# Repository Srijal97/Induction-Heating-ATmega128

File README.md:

# Induction-Heating-ATmega128
Code and other files for the control of Induction Heating of metals for temperatures up to 1200C+ for Riddhi Heatron. Control board uses the ATmega128 microcontroller.

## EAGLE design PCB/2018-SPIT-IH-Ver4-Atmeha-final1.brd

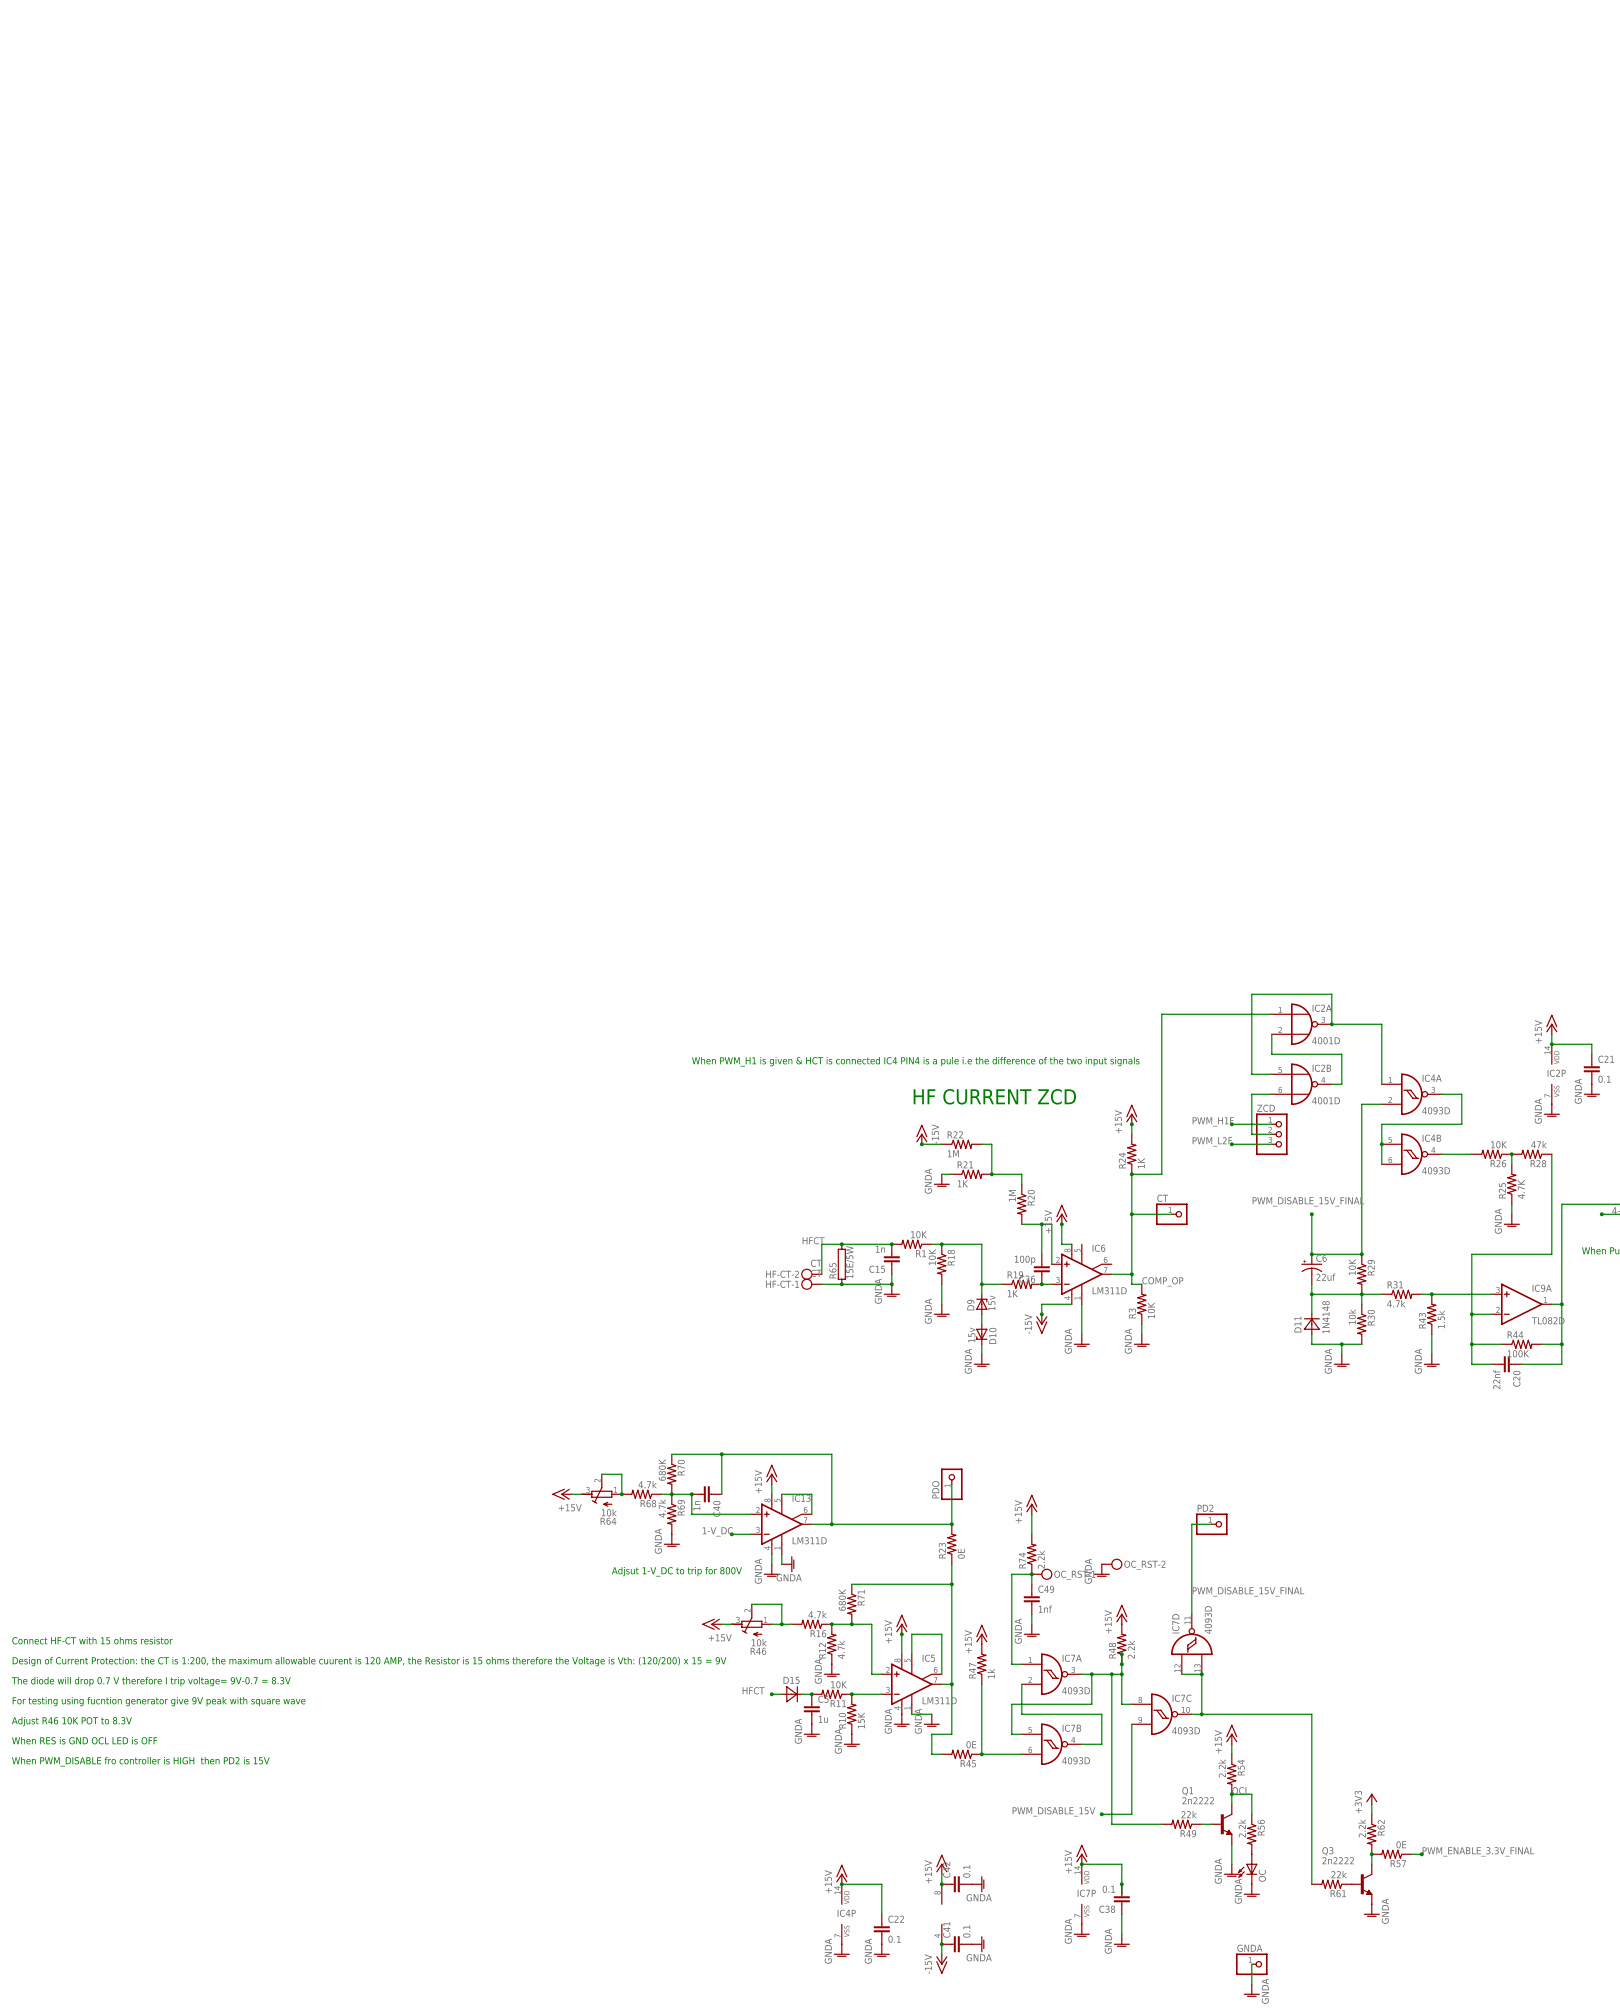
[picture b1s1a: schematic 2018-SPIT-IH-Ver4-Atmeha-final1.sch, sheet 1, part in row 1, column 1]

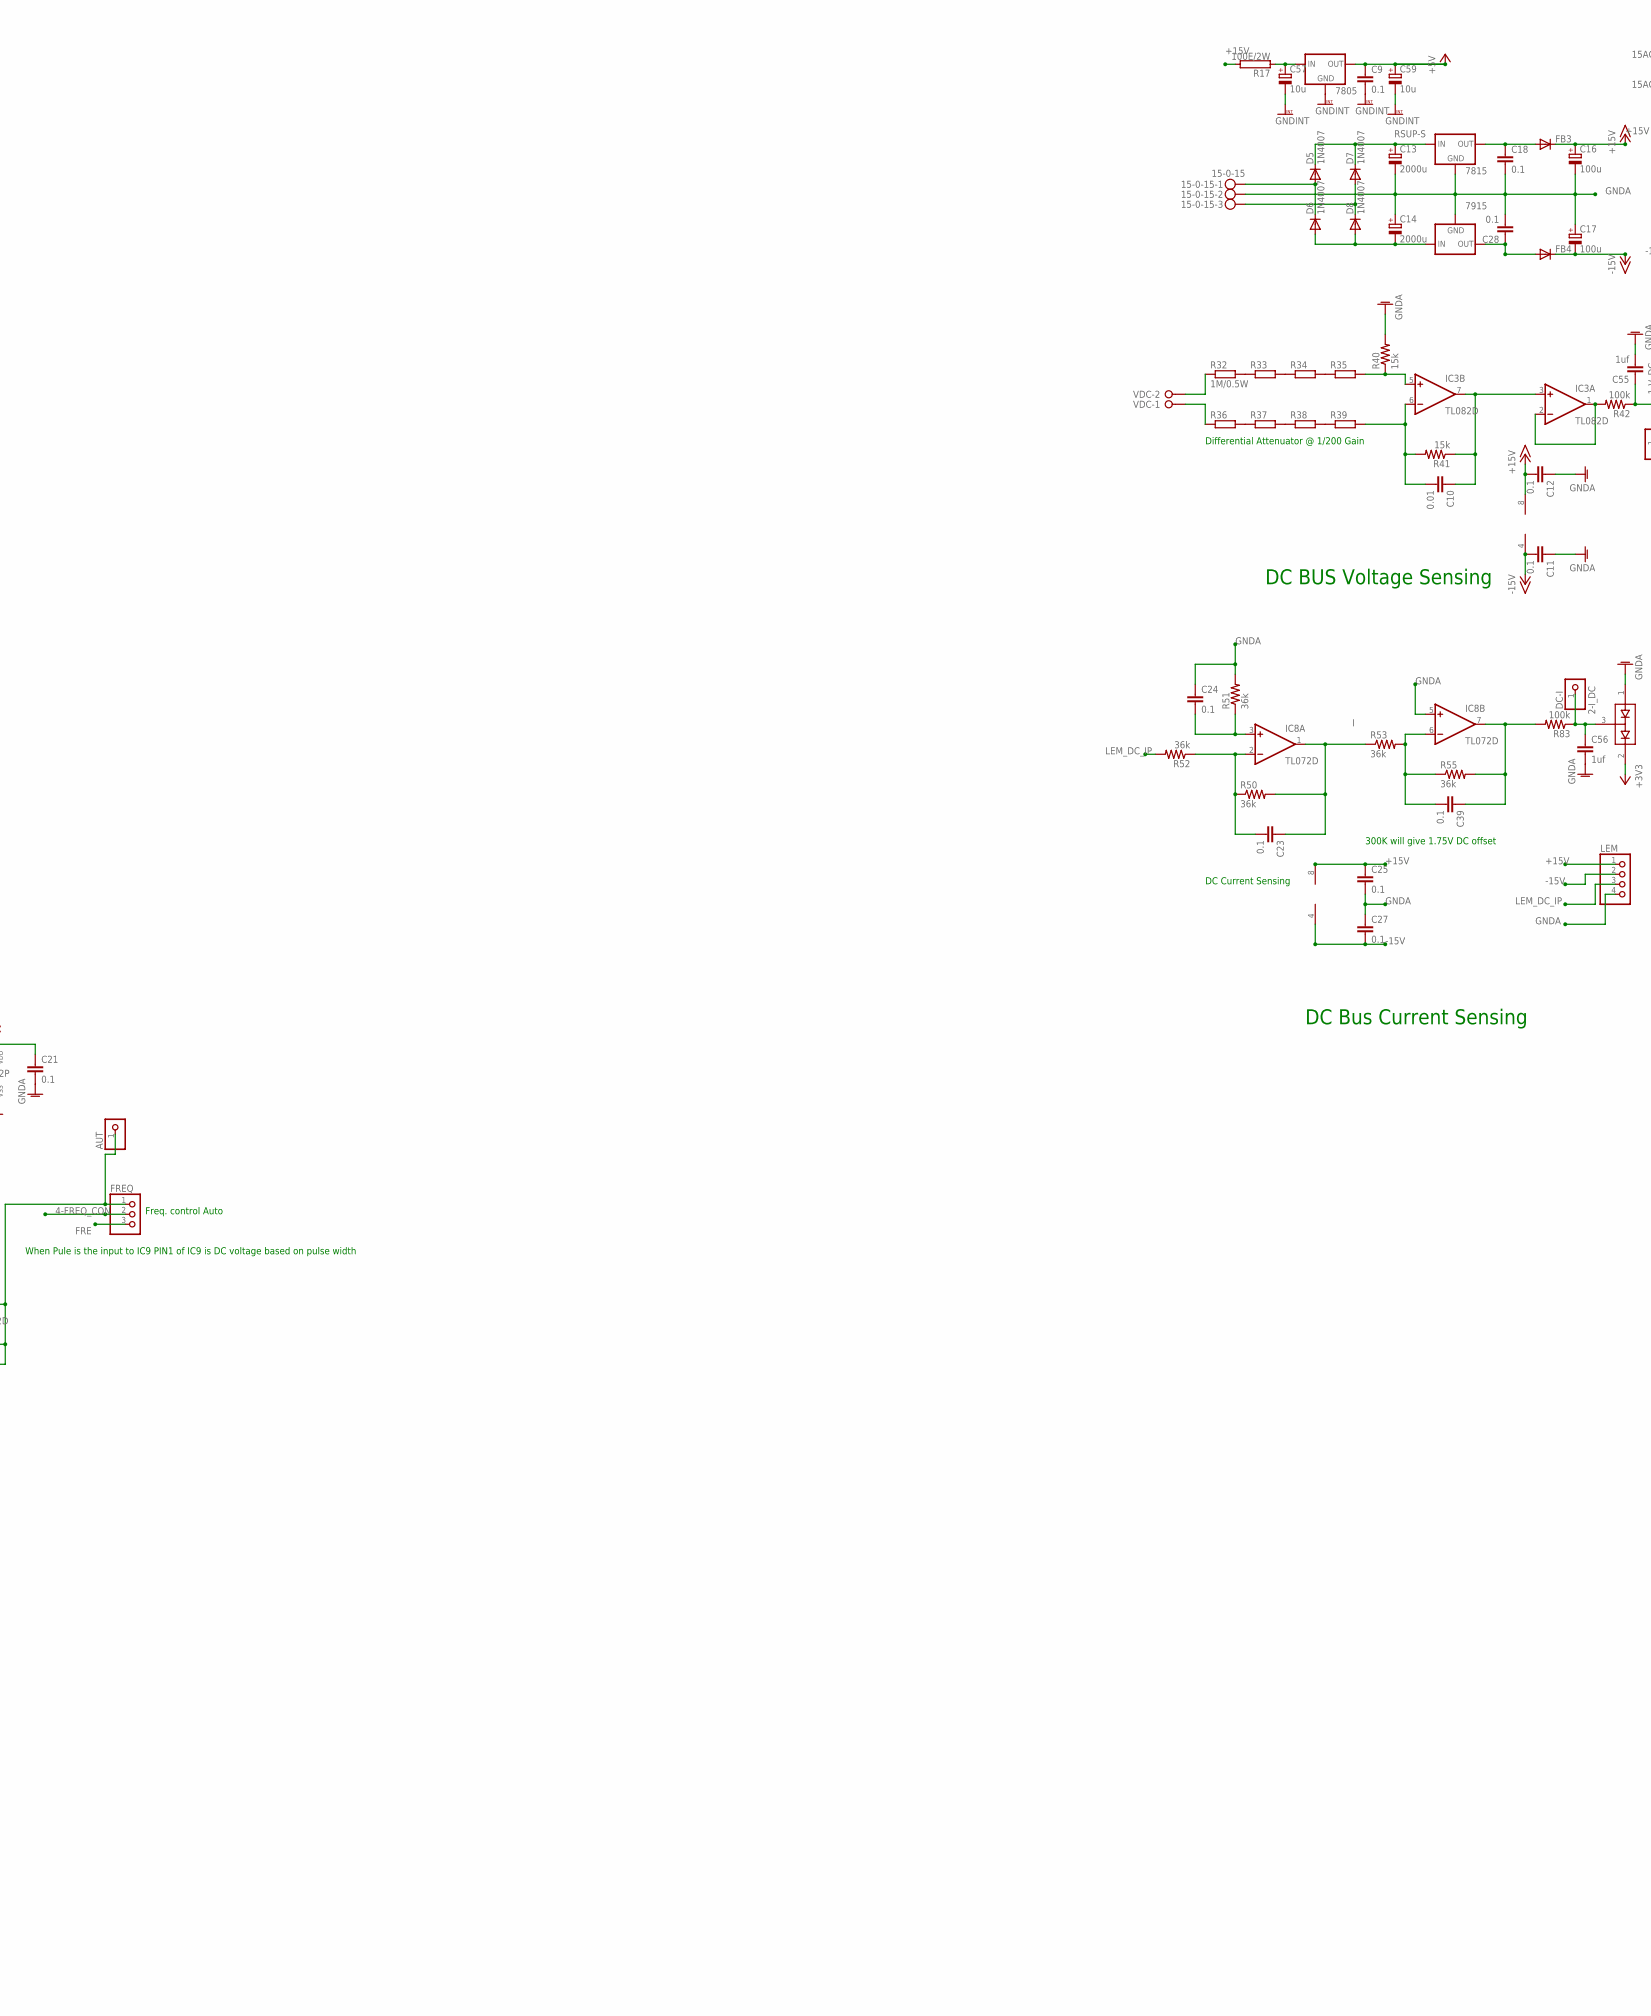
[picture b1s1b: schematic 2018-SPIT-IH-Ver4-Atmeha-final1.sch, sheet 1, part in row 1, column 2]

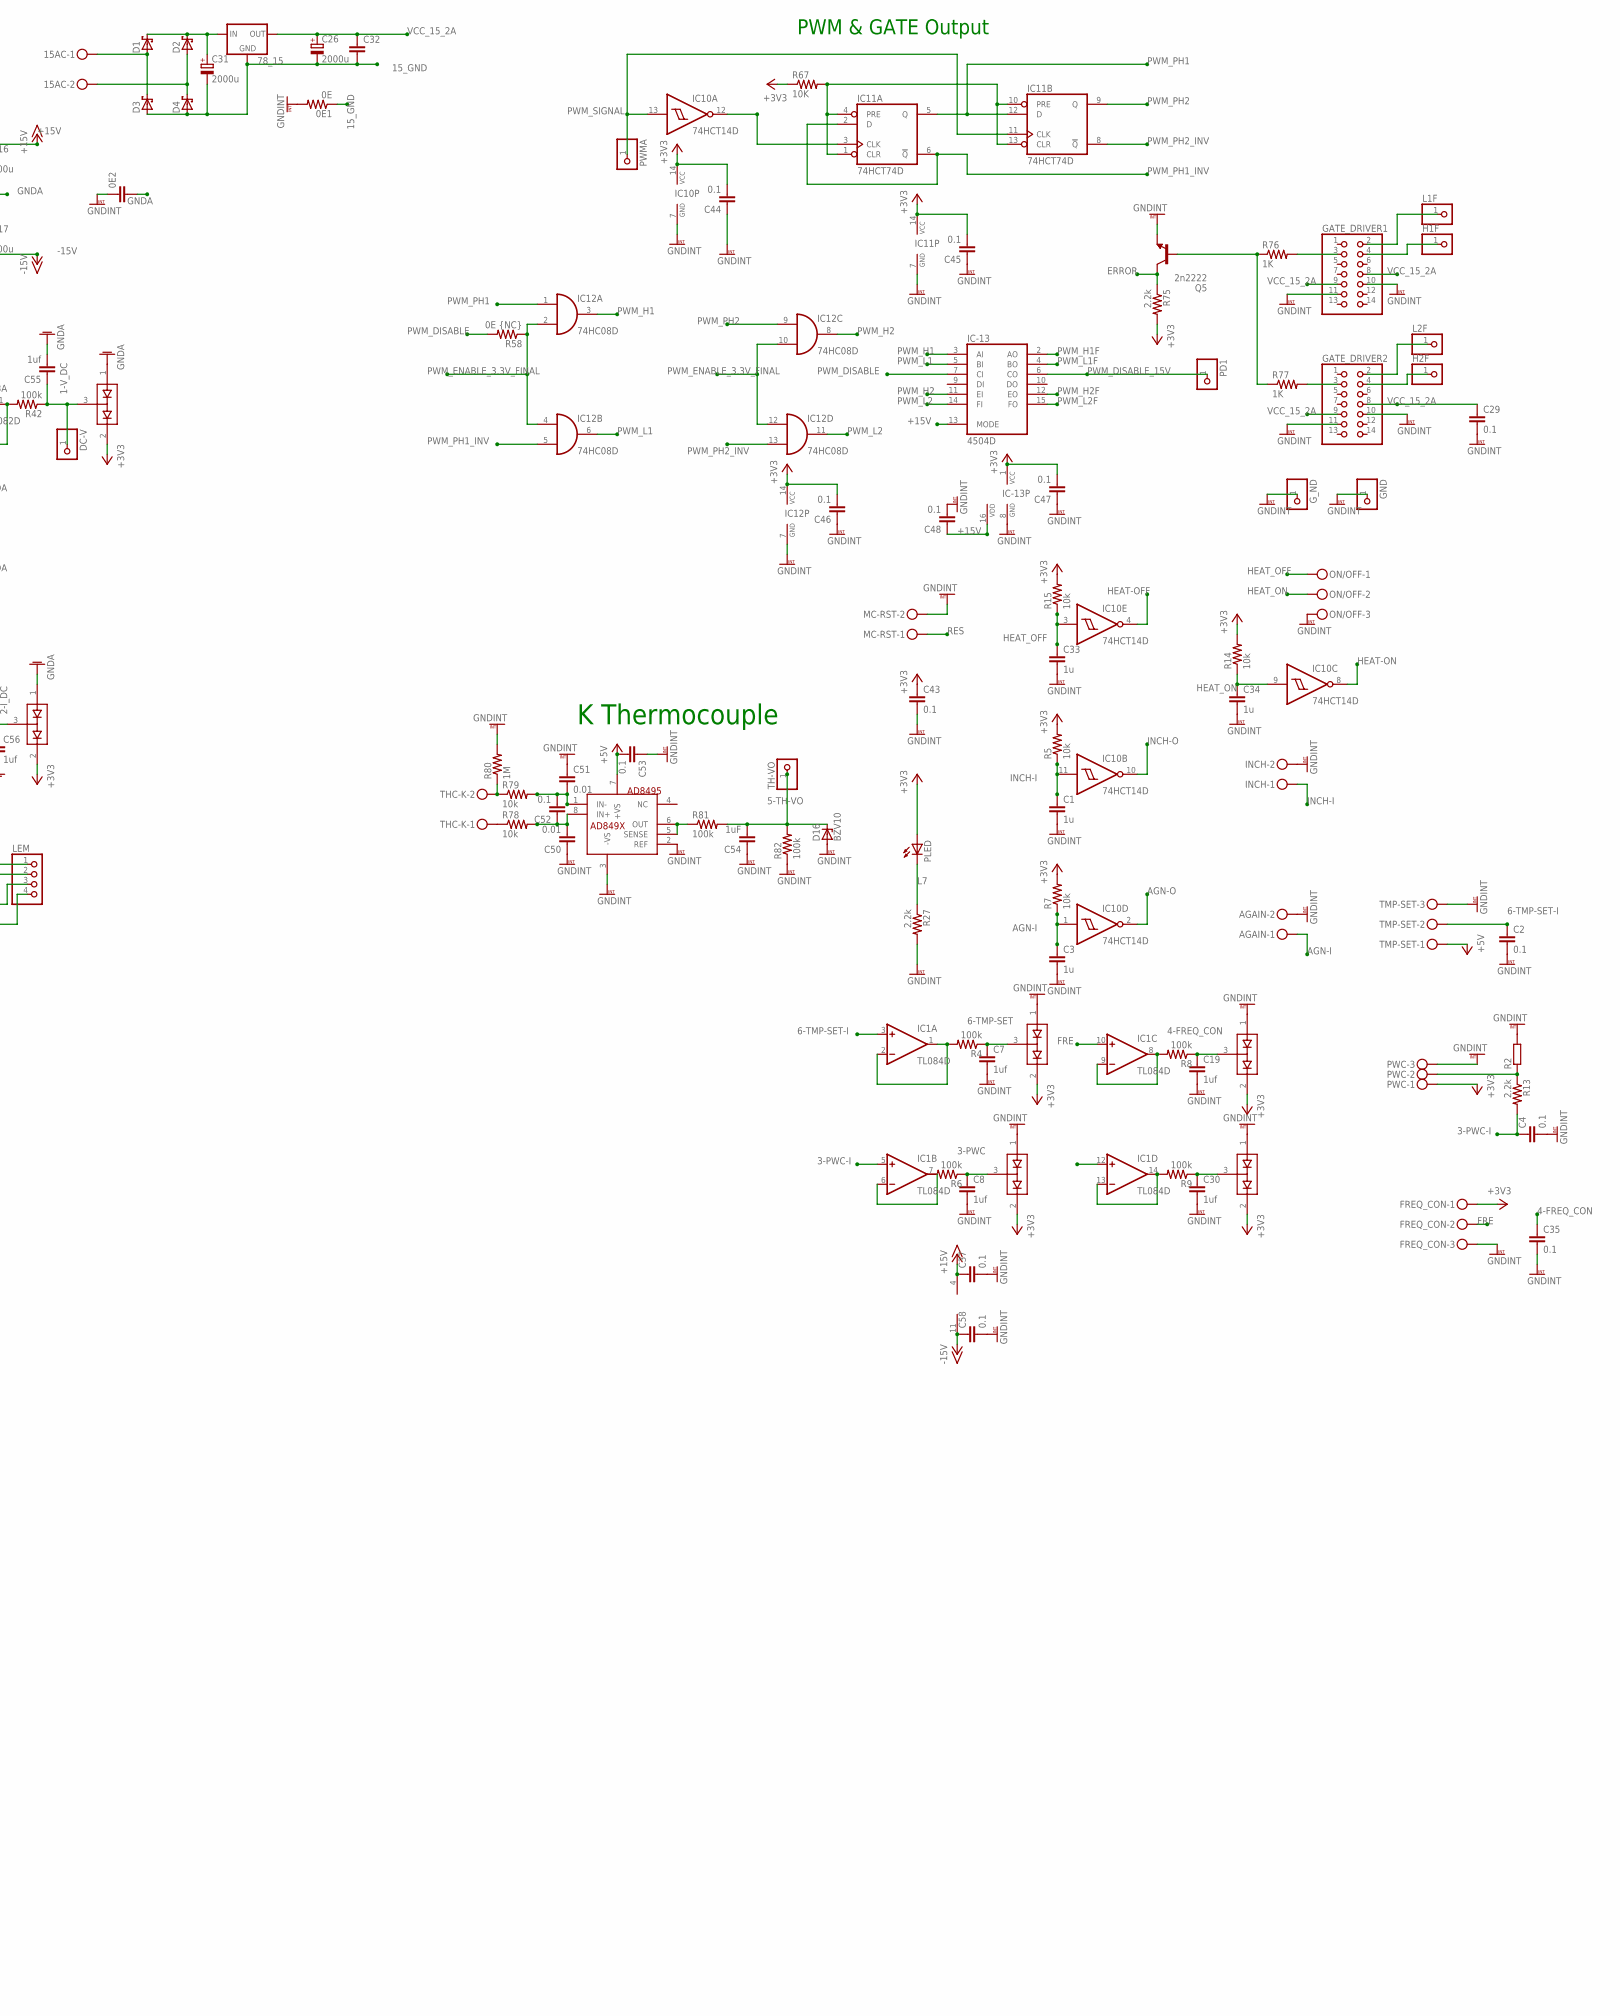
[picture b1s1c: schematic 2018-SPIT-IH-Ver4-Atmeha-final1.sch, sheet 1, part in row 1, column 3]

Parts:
0E1: 0E; M1206
0E2: C1206
15-0-15: 15-0-15; MKDSN1,5/3-5,08
15AC: MKDSN1,5/2-5,08
78_15: 78XX-TO3; TO3-78
7805, 7815: 78XXS
7915: 79XXS
AD8495: AD849X; MSOP8
AGAIN: MKDSN1,5/2-5,08; MPN MKDSN 1,5/2-5.08
AUT: PINHD-1X1; 1X01
C1, C3, C5, C33, C34: 1u; C1206
C2, C4, C9, C11, C12, C18, C21, C22, C23, C24, C25, C27, C28, C29, C35, C37, C38, C39, C41, C42, C43, C44, C45, C46, C47, C48, C52, C53, C58: 0.1; C1206
C6: 22uf; E2,5-6
C7, C8, C19, C30, C55, C56: 1uf; C1206
C10, C50, C51: 0.01; C1206
C13, C14: 2000u; E5-13
C15, C40: 1n; C1206
C16, C17: 100u; E5-8,5
C20: 22nf; C1206
C26, C31: 2000u; E7,5-18
C32: C-EU025-025X050; C025-025X050
C36: 100p; C1206
C49: 1nf; C1206
C54: 1uF; C1206
C57, C59: 10u; R/2012-12R
CT: PINHD-1X1; 1X01
D1, D2, D3, D4: C4111-15
D5, D6, D7, D8: 1N4007; DO41-10
D9, D10: 15v; DO34Z7
D11: 1N4148; SMA
D12, D14, D17, D18, D19, D20: BAV99; SOT23
D15: SMA
D16: BZV10; DO34Z7
DC-I: PINHD-1X1; 1X01
DC-V: PINHD-1X1; 1X01
FB3, FB4: SOD57-10
FREQ: PINHD-1X3; 1X03
FREQ_CON: MKDSN1,5/3-5,08
GATE_DRIVER1, GATE_DRIVER2: PINHD-2X7; 2X07
GND: PINHD-1X1; 1X01
GNDA: PINHD-1X1; 1X01
G_ND: PINHD-1X1; 1X01
H1F, H2F: PINHD-1X1; 1X01
HF-CT: CT; MKDSN1,5/2-5,08
IC1: TL084D; SO14
IC2: 4001D; SO14
IC3, IC9: TL082D; SO08
IC4, IC7: 4093D; SO14
IC5, IC6, IC13: LM311D; SO08
IC8: TL072D; SO08
IC10: 74HCT14D; SO14
IC11: 74HCT74D; SO14
IC12: 74HC08D; SO14
IC-13: 4504D; SO16
INCH: MKDSN1,5/2-5,08; MPN MKDSN 1,5/2-5.08
L1F, L2F: PINHD-1X1; 1X01
LEM: PINHD-1X4; 1X04
MC-RST: MKDSN1,5/2-5,08
OC: LEDCHIPLED_1206; CHIPLED_1206
OC_RST: MKDSN1,5/2-5,08
ON/OFF: MKDSN1,5/3-5,08
PD1, PD2: PINHD-1X1; 1X01
PDO: PINHD-1X1; 1X01
PLED: LEDCHIPLED_1206; CHIPLED_1206
PWC: MKDSN1,5/3-5,08
PWMA: PINHD-1X1; 1X01
Q1, Q3, Q5: 2n2222; SOT23-BEC
R1, R3, R11, R18, R26, R29, R67: 10K; M1206
R2, R33, R34, R35, R36, R37, R38, R39: R-EU_0309/12; 0309/12
R4, R6, R8, R9, R42, R81, R82, R83: 100k; M1206
R5, R7, R14, R15, R30, R78, R79: 10k; M1206
R10: 15K; M1206
R12, R16, R31, R68, R69: 4.7k; M1206
R13, R27, R48, R54, R56, R62, R74, R75: 2.2k; M1206
R17: 100E/2W; CA5050
R19, R21, R24, R76, R77: 1K; M1206
R20, R22, R80: 1M; M1206
R23, R45, R57: 0E; M1206
R25: 4.7K; M1206
R28: 47k; M1206
R32: 1M/0.5W; 0309/12
R40, R41: 15k; M1206
R43: 1.5k; M1206
R44: 100K; M1206
R46, R64: 10k; RTRIM64W
R47: 1k; M1206
R49, R61: 22k; M1206
R50, R51, R52, R53, R55: 36k; M1206
R58: 0E {NC}; M1206
R65: 15E/5W; MPC71-5
R70, R71: 680K; M1206
TH-VO: PINHD-1X1; 1X01
THC-K: MKDSN1,5/2-5,08
TMP-SET: MKDSN1,5/3-5,08; MPN SMKDSN1,5/3-5,08
VDC: W237-2N
ZCD: PINHD-1X3; 1X03

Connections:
1-V_DC: C55.1, D12.3 (COM), DC-V.1, IC13.3 (-IN), R42.1; also elsewhere on the board
2: C39.1, IC8.7 (OUT), R55.2, R83.2
2-I_DC: C56.1, D14.3 (COM), DC-I.1, R83.1; also elsewhere on the board
3-PWC: C8.1, D18.3 (COM), R6.1; also elsewhere on the board
3-PWC-I: C4.1, IC1.5 (+IN), R13.2
4-FREQ_CON: C19.1, C35.1, D20.3 (COM), FREQ.2, R8.1; also elsewhere on the board
5-TH-VO: C54.2, D16.C, R81.2, R82.2, TH-VO.1; also elsewhere on the board
6-TMP-SET: C7.1, D17.3 (COM), R4.1; also elsewhere on the board
6-TMP-SET-I: C2.1, IC1.3 (+IN), TMP-SET.2
15_GND: 0E1.1, 78_15.3 (GND), C26.-, C31.-, C32.2, D3.A, D4.A
+5V: 7805.OUT, AD8495.7 (+VS), C9.1, C43.1, C44.2, C45.2, C46.2, C47.2, C53.2, C59.+, D12.2 (C2), D14.2 (C2), D17.2 (C2), D18.2 (C2), D19.2 (C2), D20.2 (C2), FREQ_CON.1, IC10.14 (VCC), IC11.14 (VCC), IC12.14 (VCC), IC-13.1 (VCC), PLED.A, PWC.1, R5.2, R7.2, R14.2, R15.2, R62.1, R67.1, R75.2, TMP-SET.1; also elsewhere on the board
+15V: C12.2, C16.+, C21.1, C22.1, C25.1, C37.1, C38.2, C42.1, C48.1, FB3.C, IC1.4 (V+), IC2.14 (VDD), IC3.8 (V+), IC4.14 (VDD), IC5.8 (V+), IC6.8 (V+), IC7.14 (VDD), IC8.8 (V+), IC9.8 (V+), IC13.8 (V+), IC-13.13 (MODE), IC-13.16 (VDD), LEM.1, R17.2, R24.2, R46.3 (A), R47.2, R48.2, R54.1, R64.3 (A), R74.2
-15V: C11.2, C17.-, C27.2, C41.1, C58.1, FB4.C, IC1.11 (V-), IC3.4 (V-), IC6.4 (V-), IC8.4 (V-), IC9.4 (V-), LEM.2, R22.1
AGN-I: AGAIN.1, C3.1, IC10.1 (I), R7.1
AGN-O: IC10.2 (O); also elsewhere on the board
COMP_OP: CT.1, IC2.1 (I0), IC6.7 (OUT), R3.2, R24.1
ERROR: Q5.C, R75.1; also elsewhere on the board
FRE: FREQ.3, FREQ_CON.2, IC1.10 (+IN)
GNDA: 0E2.2, 15-0-15.2, 7815.GND, 7915.GND, C5.2, C11.1, C12.1, C13.-, C14.+, C15.1, C16.-, C17.+, C18.2, C21.2, C22.2, C24.1, C25.2, C27.1, C28.2, C38.1, C41.2, C42.2, C49.2, C55.2, C56.2, D10.C, D11.A, D12.1 (A1), D14.1 (A1), GNDA.1, HF-CT.1, IC2.7 (VSS), IC4.7 (VSS), IC5.1 (GND), IC5.4 (V-), IC6.1 (GND), IC7.7 (VSS), IC8.5 (+IN), IC13.1 (GND), IC13.4 (V-), LEM.4, OC.C, OC_RST.2, Q1.E, Q3.E, R3.1, R10.1, R12.1, R18.2, R21.1, R25.1, R30.2, R40.2, R43.1, R51.2, R65.1, R69.2
GNDINT: 0E1.2, 0E2.1, 7805.GND, AD8495.2 (REF), AD8495.3 (-VS), AGAIN.2, C1.2, C2.2, C3.2, C4.2, C7.2, C8.2, C9.2, C19.2, C29.2, C30.2, C33.2, C34.2, C35.2, C37.2, C43.2, C44.1, C45.1, C46.1, C47.1, C48.2, C50.1, C51.1, C53.1, C54.1, C57.-, C58.2, C59.-, D16.A, D17.1 (A1), D18.1 (A1), D19.1 (A1), D20.1 (A1), FREQ_CON.3, GATE_DRIVER1.10, GATE_DRIVER1.11, GATE_DRIVER2.10, GATE_DRIVER2.11, GND.1, G_ND.1, IC10.7 (GND), IC11.7 (GND), IC12.7 (GND), IC-13.8 (GND), INCH.2, MC-RST.2, ON/OFF.3, PWC.3, Q5.E, R2.2, R27.2, R80.2, R82.1, TMP-SET.3; also elsewhere on the board
HEAT-OFF: IC10.4 (O); also elsewhere on the board
HEAT-ON: IC10.8 (O); also elsewhere on the board
HEAT_OFF: C33.1, IC10.3 (I), ON/OFF.1, R15.1
HEAT_ON: C34.1, IC10.9 (I), ON/OFF.2, R14.1
HFCT: C15.2, D15.A, HF-CT.2, R1.2, R65.2
I: C23.1, IC8.1 (OUT), R50.2, R53.1
INCH-I: C1.1, IC10.11 (I), INCH.1, R5.1
INCH-O: IC10.10 (O); also elsewhere on the board
L7: PLED.C, R27.1
LEM_DC_IP: LEM.3, R52.2
unnamed: IC1.1 (OUT), IC1.2 (-IN), R4.2
unnamed: IC4.3 (O), IC4.5 (I0), IC4.6 (I1)
unnamed: IC1.6 (-IN), IC1.7 (OUT)
unnamed: IC1.8 (OUT), IC1.9 (-IN), R8.2
unnamed: C49.1, IC7.1 (I0), OC_RST.1, R74.1
unnamed: IC1.13 (-IN), IC1.14 (OUT), R9.2
unnamed: IC2.2 (I1), IC2.4 (O)
unnamed: IC4.4 (O), R26.2
unnamed: AUT.1, C20.1, FREQ.1, IC9.1 (OUT), R44.2
unnamed: 15-0-15.1, D5.A, D6.C
unnamed: AD8495.8 (IN+), C50.2, C52.1, R78.2
unnamed: IC5.2 (+IN), R12.2, R16.1, R71.2
unnamed: IC2.3 (O), IC2.5 (I0), IC4.1 (I0)
unnamed: IC10.12 (O), IC11.3 (CLK)
unnamed: IC5.5 (ON), IC5.6 (ON/STR)
unnamed: IC5.3 (-IN), R10.2, R11.1
unnamed: PWC.2, R2.1, R13.1
unnamed: IC11.1 (CLR), IC11.4 (PRE), IC11.10 (PRE), IC11.13 (CLR), R67.2
unnamed: GATE_DRIVER1.3, R76.2
unnamed: IC5.7 (OUT), R23.1, R45.2, R71.1
unnamed: IC7.6 (I1), R45.1, R47.1
unnamed: C5.1, D15.C, R11.2
unnamed: R32.2, R33.1
unnamed: R33.2, R34.1
unnamed: R34.2, R35.1
unnamed: R36.2, R37.1
unnamed: 15-0-15.3, D7.A, D8.C
unnamed: 7915.IN, C14.-, D6.A, D8.A
unnamed: D9.C, R1.1, R18.1, R19.1
unnamed: 7805.IN, C57.+, R17.1
unnamed: 7815.OUT, C18.1, FB3.A
unnamed: R37.2, R38.1
unnamed: 7915.OUT, C28.1, FB4.A
unnamed: D9.A, D10.A
unnamed: R38.2, R39.1
unnamed: C36.1, IC6.3 (-IN), R19.2
unnamed: C36.2, IC6.2 (+IN), R20.2
unnamed: R20.1, R21.2, R22.2
unnamed: R16.2, R46.1 (E), R46.2 (S)
unnamed: R32.1, VDC.2
unnamed: Q1.B, R49.1
unnamed: R36.1, VDC.1
unnamed: IC3.5 (+IN), R35.2, R40.1
unnamed: IC7.3 (O), IC7.5 (I0), IC7.8 (I0), R48.1, R49.2
unnamed: IC7.2 (I1), IC7.4 (O)
unnamed: C10.2, IC3.6 (-IN), R39.2, R41.2
unnamed: C10.1, IC3.3 (+IN), IC3.7 (OUT), R41.1
unnamed: R25.2, R26.1, R28.2
unnamed: IC3.1 (OUT), IC3.2 (-IN), R42.2
unnamed: AD8495.1 (IN-), C51.2, C52.2, R79.2
unnamed: IC7.10 (O), IC7.12 (I0), IC7.13 (I1), R61.2
unnamed: C6.-, D11.C, R29.2, R30.1, R31.1
unnamed: OC.A, R56.2
unnamed: IC2.6 (I1), ZCD.2
unnamed: IC9.3 (+IN), R31.2, R43.2
unnamed: GATE_DRIVER2.3, R77.2
unnamed: C20.2, IC9.2 (-IN), R28.1, R44.1
unnamed: Q3.B, R61.1
unnamed: C23.2, IC8.2 (-IN), R50.1, R52.1
unnamed: C24.2, IC8.3 (+IN), R51.1
unnamed: R78.1, THC-K.1
unnamed: C39.2, IC8.6 (-IN), R53.2, R55.1
unnamed: Q3.C, R57.2, R62.2
unnamed: IC13.5 (ON), IC13.6 (ON/STR)
unnamed: Q5.B, R76.1, R77.1
unnamed: R79.1, R80.1, THC-K.2
unnamed: R64.1 (E), R64.2 (S), R68.2
unnamed: C40.2, IC13.2 (+IN), R68.1, R69.1, R70.2
unnamed: C40.1, IC13.7 (OUT), PDO.1, R23.2, R70.1
unnamed: AD8495.5 (SENSE), AD8495.6 (OUT), R81.1
unnamed: C30.1, D19.3 (COM), R9.1
unnamed: 15AC.1, D1.A, D3.C
unnamed: 15AC.2, D2.A, D4.C
unnamed: 78_15.2 (IN), C31.+, D1.C, D2.C
OCL: Q1.C, R54.2, R56.1
PWM_DISABLE: IC-13.7 (CI), R58.2; also elsewhere on the board
PWM_DISABLE_15V: IC7.9 (I1), IC-13.6 (CO), PD1.1
PWM_DISABLE_15V_FINAL: C6.+, IC4.2 (I1), IC7.11 (O), PD2.1, R29.1
PWM_ENABLE_3.3V_FINAL: IC12.2 (I1), IC12.4 (I0), IC12.10 (I1), IC12.12 (I0), R57.1, R58.1; also elsewhere on the board
PWM_H1: IC12.3 (O), IC-13.3 (AI)
PWM_H1F: GATE_DRIVER1.4, H1F.1, IC-13.2 (AO), ZCD.1
PWM_H2: IC12.8 (O), IC-13.11 (EI)
PWM_H2F: GATE_DRIVER2.4, H2F.1, IC-13.12 (EO)
PWM_L1: IC12.6 (O), IC-13.5 (BI)
PWM_L1F: GATE_DRIVER1.2, IC-13.4 (BO), L1F.1
PWM_L2: IC12.11 (O), IC-13.14 (FI)
PWM_L2F: GATE_DRIVER2.2, IC-13.15 (FO), L2F.1, ZCD.3
PWM_PH1: IC11.5 (Q), IC11.12 (D), IC12.1 (I0)
PWM_PH1_INV: IC11.2 (D), IC11.6 (!Q), IC12.5 (I1)
PWM_PH2: IC11.9 (Q), IC12.9 (I0)
PWM_PH2_INV: IC11.8 (!Q), IC12.13 (I1)
PWM_SIGNAL: IC10.13 (I), IC11.11 (CLK), PWMA.1; also elsewhere on the board
RES: MC-RST.1; also elsewhere on the board
RSUP-S: 7815.IN, C13.+, D5.C, D7.C
VCC_15_2A: 78_15.1 (OUT), C26.+, C29.1, C32.1, GATE_DRIVER1.8, GATE_DRIVER1.9, GATE_DRIVER2.8, GATE_DRIVER2.9

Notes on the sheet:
300K will give 1.75V DC offset
Differential Attenuator @ 1/200 Gain
DC Current Sensing
HF CURRENT ZCD
Freq. control Auto
PWM & GATE Output
DC BUS Voltage Sensing
DC Bus Current Sensing
When RES is GND OCL LED is OFF
When PWM_DISABLE fro controller is HIGH then PD2 is 15V
When PWM_H1 is given & HCT is connected IC4 PIN4 is a pule i.e the difference of the two input signals
When Pule is the input to IC9 PIN1 of IC9 is DC voltage based on pulse width
K Thermocouple
Design of Current Protection: the CT is 1:200, the maximum allowable cuurent is 120 AMP, the Resistor is 15 ohms therefore the Voltage is Vth: (120/200) x 15 = 9V
The diode will drop 0.7 V therefore I trip voltage= 9V-0.7 = 8.3V
For testing using fucntion generator give 9V peak with square wave
Adjust R46 10K POT to 8.3V
Adjsut 1-V_DC to trip for 800V
Connect HF-CT with 15 ohms resistor

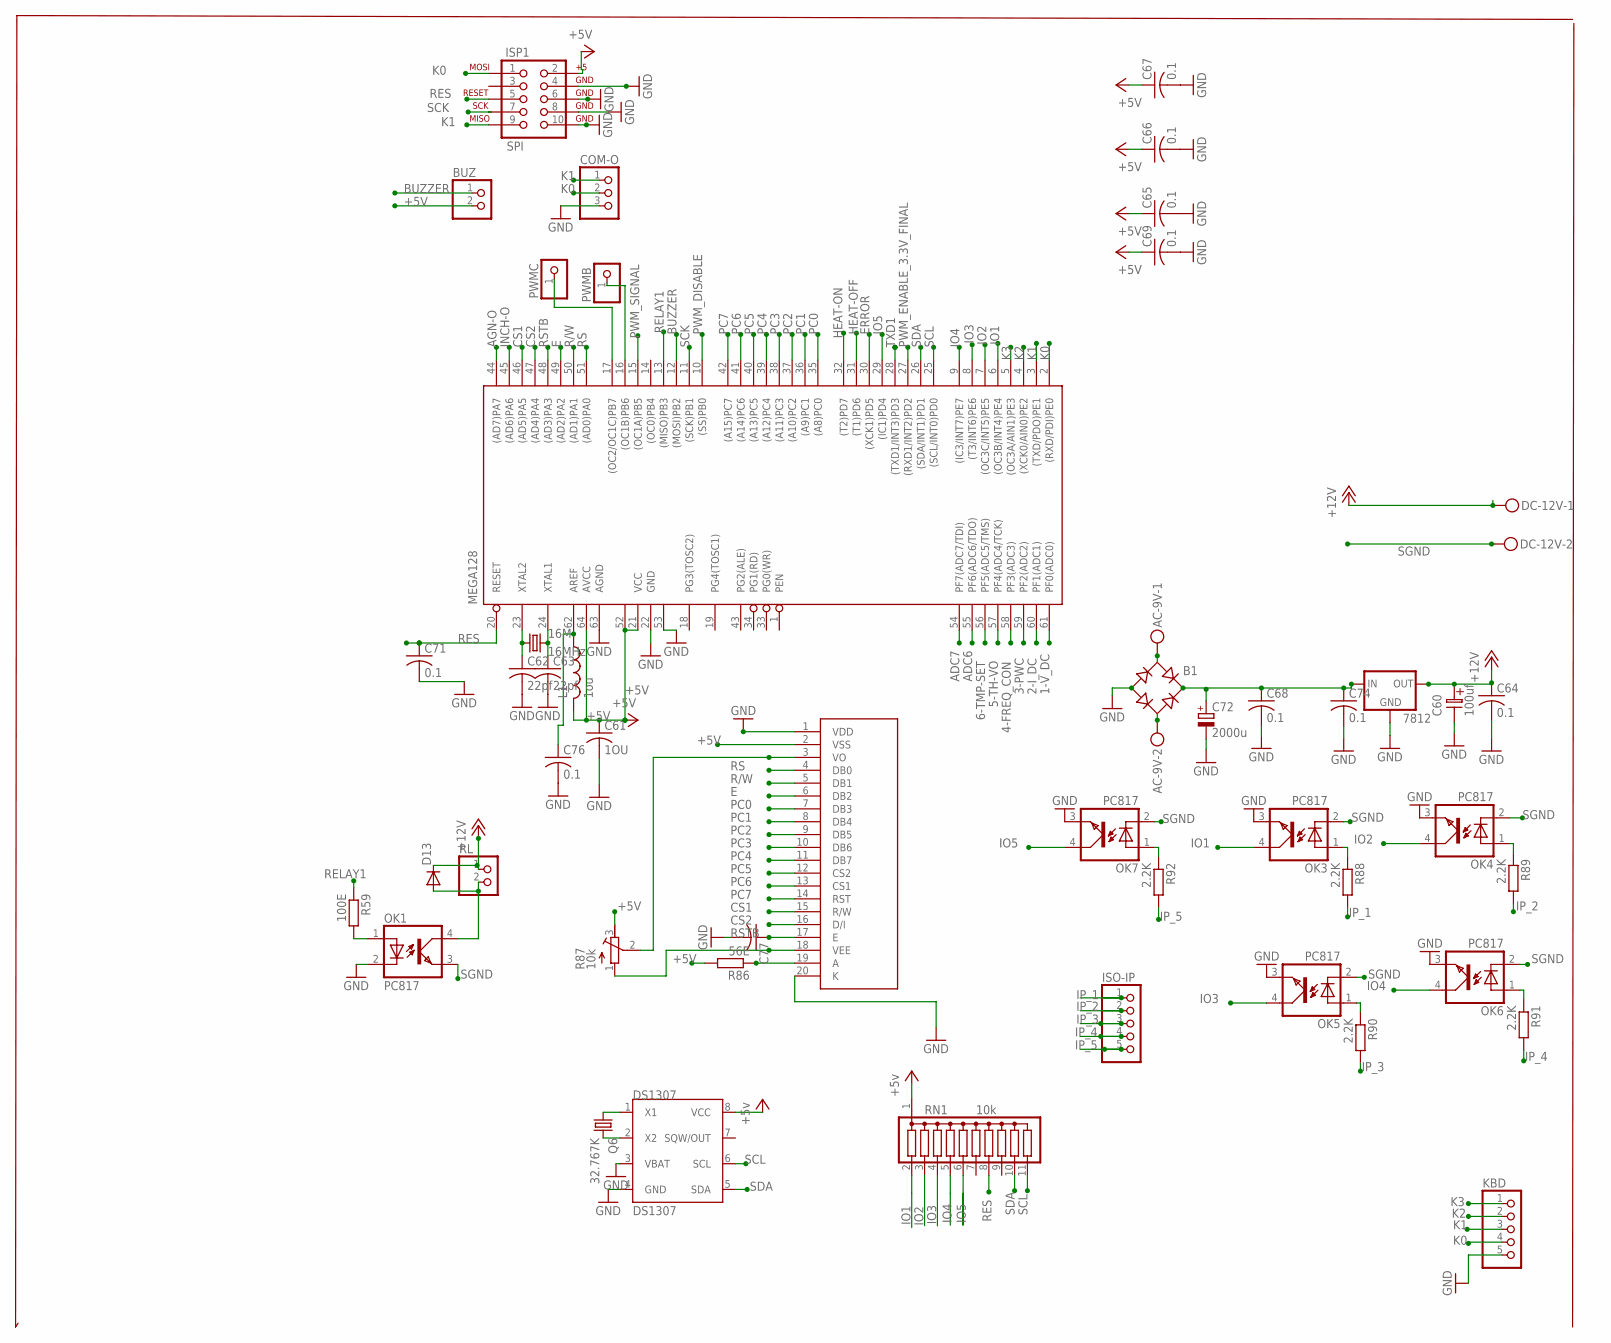
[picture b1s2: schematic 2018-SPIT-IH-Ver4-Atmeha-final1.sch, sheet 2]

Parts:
16M: 16MHz; HC49/S
7812: 78XXS
AC-9V: MKDSN1,5/2-5,08
B1: RB1A
BUZ: PINHD-1X2; 1X02
C60: 100uf; ES-2,5
C61: 1OU; C1206
C62, C63: 22pf; C1206
C64, C65, C66, C67, C68, C69, C71, C74, C76: 0.1; C1206
C72: 2000u; E5-10,5
C77: C-USC1206; C1206
COM-O: PINHD-1X3; 1X03
D13: DO41-10
DC-12V: MKDSN1,5/2-5,08
DS1307: DS1307; SOIC-8
GLCD: LCD-G12864BARE; 1X20
ISO-IP: PINHD-1X5; 1X05
ISP1: SPI; 2X5-SHROUDED_LOCK
KBD: PINHD-1X5; 1X05
L1: 1ou; 0207/10
MEGA128: TQFP64
OK1, OK3, OK4, OK5, OK6, OK7: PC817; DIL04; MPN PC817X4J000F
PWMB: PINHD-1X1; 1X01
PWMC: PINHD-1X1; 1X01
Q6: 32.767K; TC26H
R59: 100E; M1206
R86: 56E; M1206
R87: 10k; RTRIM64W
R88, R89, R90, R91, R92: 2.2K; M1206
RL: PINHD-1X2; 1X02
RN1: 10k; SIL11

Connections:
1-V_DC: MEGA128.61 (PF0(ADC0)); also elsewhere on the board
2-I_DC: MEGA128.60 (PF1(ADC1)); also elsewhere on the board
3-PWC: MEGA128.59 (PF2(ADC2)); also elsewhere on the board
4-FREQ_CON: MEGA128.58 (PF3(ADC3)); also elsewhere on the board
5-TH-VO: MEGA128.57 (PF4(ADC4/TCK)); also elsewhere on the board
6-TMP-SET: MEGA128.56 (PF5(ADC5/TMS)); also elsewhere on the board
+5V: BUZ.2, C61.1, C65.1, C66.1, C67.1, C69.1, DS1307.8 (VCC), GLCD.2 (VSS), ISP1.2, L1.2, MEGA128.21 (VCC), MEGA128.52 (VCC1), MEGA128.64 (AVCC), R86.2, R87.3 (A), RN1.1; also elsewhere on the board
+12V: 7812.OUT, C60.1, C64.1, D13.C, DC-12V.1, RL.1
ADC6: MEGA128.55 (PF6(ADC6/TDO))
ADC7: MEGA128.54 (PF7(ADC7/TDI))
AGN-O: MEGA128.44 ((AD7)PA7); also elsewhere on the board
BUZZER: BUZ.1, MEGA128.12 ((MOSI)PB2)
CS1: GLCD.15 (R/W), MEGA128.46 ((AD5)PA5)
CS2: GLCD.16 (D/I), MEGA128.47 ((AD4)PA4)
E: GLCD.6 (DB2), MEGA128.49 ((AD2)PA2)
ERROR: MEGA128.30 ((XCK1)PD5); also elsewhere on the board
GNDINT: C61.2, C62.2, C63.2, C65.2, C66.2, C67.2, C69.2, C71.2, C76.2, C77.2, COM-O.3, DS1307.3 (VBAT), DS1307.4 (GND), GLCD.1 (VDD), GLCD.20 (K), ISP1.4, ISP1.6, ISP1.8, ISP1.10, KBD.5, MEGA128.22 (GND), MEGA128.53 (GND1), MEGA128.63 (AGND), OK1.2 (C), OK3.3 (EMIT), OK4.3 (EMIT), OK5.3 (EMIT), OK6.3 (EMIT), OK7.3 (EMIT); also elsewhere on the board
HEAT-OFF: MEGA128.31 ((T1)PD6); also elsewhere on the board
HEAT-ON: MEGA128.32 ((T2)PD7); also elsewhere on the board
INCH-O: MEGA128.45 ((AD6)PA6); also elsewhere on the board
IO1: MEGA128.6 ((OC3B/INT4)PE4), OK3.4 (COL), RN1.2
IO2: MEGA128.7 ((OC3C/INT5)PE5), OK4.4 (COL), RN1.3
IO3: MEGA128.8 ((T3/INT6)PE6), OK5.4 (COL), RN1.4
IO4: MEGA128.9 ((IC3/INT7)PE7), OK6.4 (COL), RN1.5
IO5: MEGA128.29 ((IC1)PD4), OK7.4 (COL), RN1.6
IP_1: ISO-IP.1, R88.2
IP_2: ISO-IP.2, R89.2
IP_3: ISO-IP.3, R90.2
IP_4: ISO-IP.4, R91.2
IP_5: ISO-IP.5, R92.2
K0: COM-O.2, ISP1.1, KBD.4, MEGA128.2 ((RXD/PDI)PE0)
K1: COM-O.1, ISP1.9, KBD.3, MEGA128.3 ((TXD/PDO)PE1)
K2: KBD.2, MEGA128.4 ((XCK0/AIN0)PE2)
K3: KBD.1, MEGA128.5 ((OC3A/AIN1)PE3)
unnamed: OK1.1 (A), R59.2
unnamed: D13.A, OK1.4 (COL), RL.2
unnamed: MEGA128.16 ((OC1B)PB6), PWMB.1
unnamed: MEGA128.17 ((OC2/OC1C)PB7), PWMC.1
unnamed: 16M.1, C62.1, MEGA128.23 (XTAL2)
unnamed: 16M.2, C63.1, MEGA128.24 (XTAL1)
unnamed: GLCD.3 (VO), R87.2 (S)
unnamed: GLCD.18 (VEE), R87.1 (E)
unnamed: GLCD.19 (A), R86.1
unnamed: OK3.1 (A), R88.1
unnamed: OK4.1 (A), R89.1
unnamed: OK5.1 (A), R90.1
unnamed: OK6.1 (A), R91.1
unnamed: OK7.1 (A), R92.1
unnamed: DS1307.2 (X2), Q6.2
unnamed: DS1307.1 (X1), Q6.1
unnamed: AC-9V.1, B1.AC1
unnamed: AC-9V.2, B1.AC2
unnamed: C76.1, L1.1, MEGA128.62 (AREF)
unnamed: 7812.IN, B1.+, C68.1, C72.+, C74.1
PC0: GLCD.7 (DB3), MEGA128.35 ((A8)PC0)
PC1: GLCD.8 (DB4), MEGA128.36 ((A9)PC1)
PC2: GLCD.9 (DB5), MEGA128.37 ((A10)PC2)
PC3: GLCD.10 (DB6), MEGA128.38 ((A11)PC3)
PC4: GLCD.11 (DB7), MEGA128.39 ((A12)PC4)
PC5: GLCD.12 (CS2), MEGA128.40 ((A13)PC5)
PC6: GLCD.13 (CS1), MEGA128.41 ((A14)PC6)
PC7: GLCD.14 (RST), MEGA128.42 ((A15)PC7)
PWM_DISABLE: MEGA128.10 ((SS)PB0); also elsewhere on the board
PWM_ENABLE_3.3V_FINAL: MEGA128.27 ((RXD1/INT2)PD2); also elsewhere on the board
PWM_SIGNAL: MEGA128.15 ((OC1A)PB5); also elsewhere on the board
R/W: GLCD.5 (DB1), MEGA128.50 ((AD1)PA1)
RELAY1: MEGA128.13 ((MISO)PB3), R59.1
RES: C71.1, ISP1.5, MEGA128.20 (RESET), RN1.8; also elsewhere on the board
RS: GLCD.4 (DB0), MEGA128.51 ((AD0)PA0)
RSTB: C77.1, GLCD.17 (E), MEGA128.48 ((AD3)PA3)
SCK: ISP1.7, MEGA128.11 ((SCK)PB1)
SCL: DS1307.6 (SCL), MEGA128.25 ((SCL/INT0)PD0), RN1.11
SDA: DS1307.5 (SDA), MEGA128.26 ((SDA/INT1)PD1), RN1.10
SGND: 7812.GND, B1.-, C60.2, C64.2, C68.2, C72.-, C74.2, DC-12V.2, OK1.3 (EMIT), OK3.2 (C), OK4.2 (C), OK5.2 (C), OK6.2 (C), OK7.2 (C)
TXD1: MEGA128.28 ((TXD1/INT3)PD3)

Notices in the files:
parts and their libraries:
SparkFun-DiscreteSemi: Licensing: Creative Commons ShareAlike 4.0 International - https://creativecommons.org/licenses/by-sa/4.0
